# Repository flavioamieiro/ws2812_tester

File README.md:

A simple tester for ws2812 LED strips.

Just plug into USB for power, connect to an LED strip and check if everything
is working.

The software in this repository is licensed under the GPLv2 and the hardware
under the CERN-OHL-S v2.

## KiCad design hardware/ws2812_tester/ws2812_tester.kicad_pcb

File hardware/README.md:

Kicad project with schematics and PCB layout for the ws2812 tester project.

This source describes Open Hardware and is licensed under the CERN-OHL-S v2.
You may redistribute and modify this source and make products using it under
the terms of the CERN-OHL-S v2 (https://ohwr.org/cern_ohl_s_v2.txt).

This source is distributed WITHOUT ANY EXPRESS OR IMPLIED WARRANTY, INCLUDING
OF MERCHANTABILITY, SATISFACTORY QUALITY AND FITNESS FOR A PARTICULAR PURPOSE.
Please see the CERN-OHL-S v2 for applicable conditions.

Source location: https://github.com/flavioamieiro/ws2812_tester

As per CERN-OHL-S v2 section 4, should You produce hardware based on this
source, You must where practicable maintain the Source Location visible on the
external case of the Gizmo or other products you make using this source.

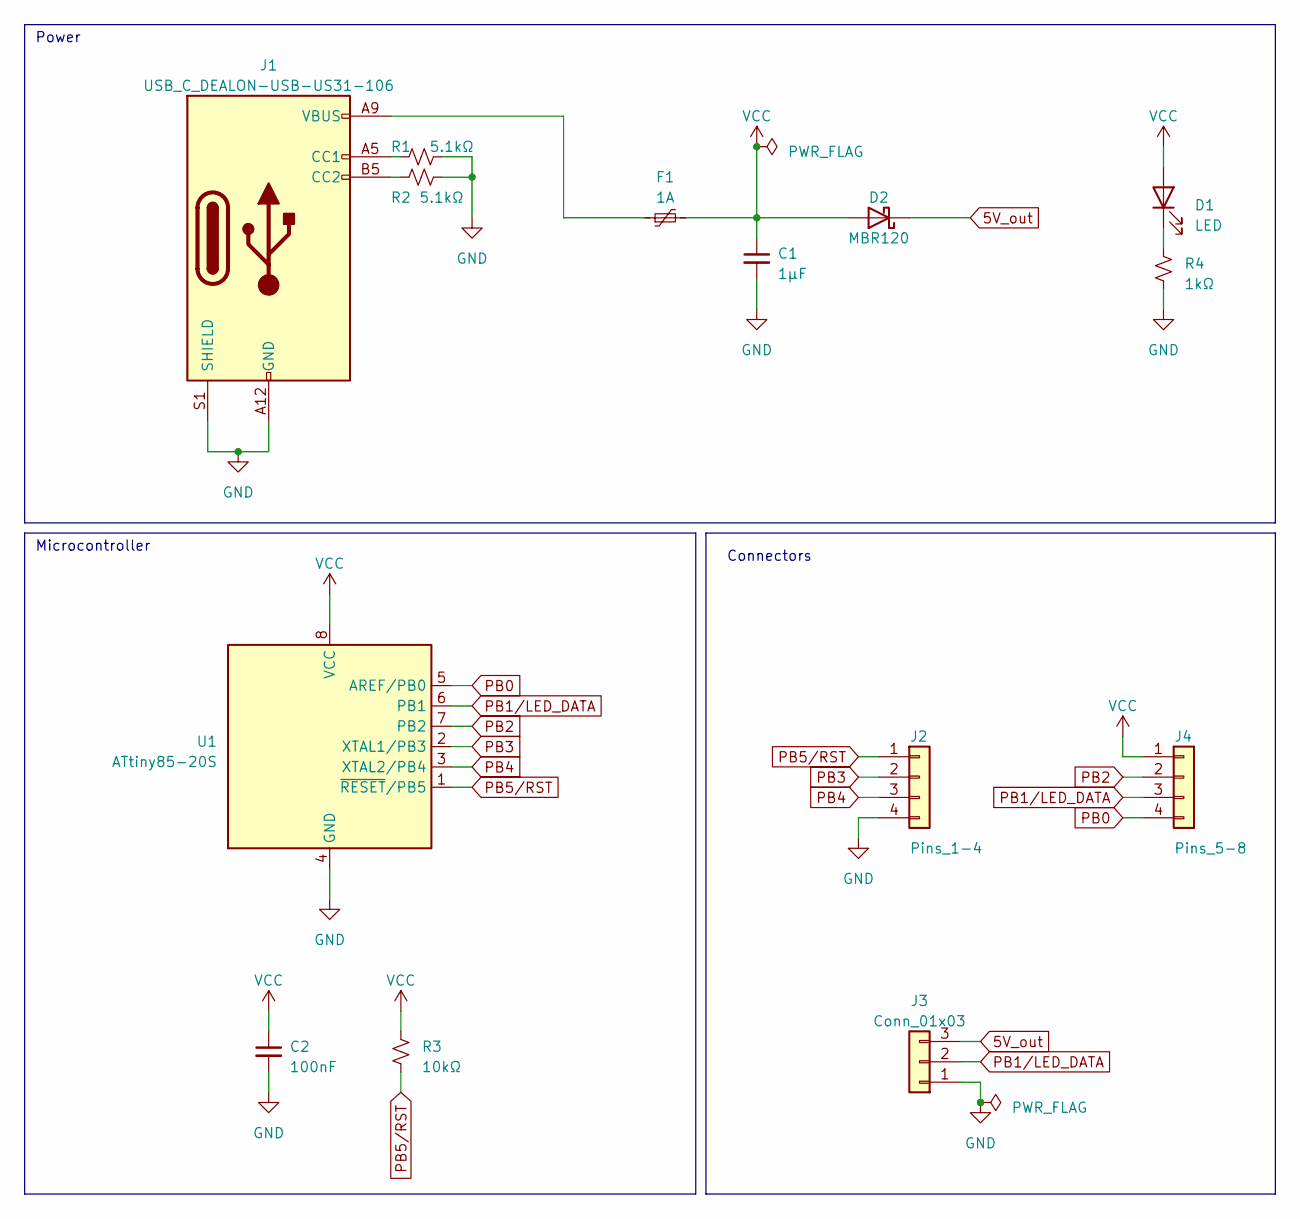
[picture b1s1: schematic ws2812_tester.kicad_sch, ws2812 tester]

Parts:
C1: 1µF; C_0805_2012Metric_Pad1.18x1.45mm_HandSolder
C2: 100nF; C_0805_2012Metric_Pad1.18x1.45mm_HandSolder
D1: LED; LED_0603_1608Metric_Pad1.05x0.95mm_HandSolder
D2: MBR120; D_SOD-123
F1: 1A; Belfuse_0ZCJ
J1: USB_C_DEALON-USB-US31-106; DEALON_USB-US31-106
J2: Pins_1-4; PinHeader_1x04_P2.54mm_Vertical
J3: Conn_01x03; PinHeader_1x03_P2.54mm_Horizontal
J4: Pins_5-8; PinHeader_1x04_P2.54mm_Vertical
R1, R2: 5.1kΩ; R_0805_2012Metric_Pad1.20x1.40mm_HandSolder
R3: 10kΩ; R_0805_2012Metric_Pad1.20x1.40mm_HandSolder
R4: 1kΩ; R_0805_2012Metric_Pad1.20x1.40mm_HandSolder
U1: ATtiny85-20S; SOIC-8W_5.3x5.3mm_P1.27mm

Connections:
5V_out: D2.1 (K), J3.3
GND: C1.2, C2.2, J1.A12 (GND), J1.B12 (GND), J1.S1 (SHIELD), J2.4, J3.1, R1.2, R2.2, R4.2, U1.4 (GND)
unnamed: D1.1 (K), R4.1
unnamed: J1.A5 (CC1), R1.1
unnamed: J1.B5 (CC2), R2.1
unnamed: F1.1, J1.A9 (VBUS), J1.B9 (VBUS)
PB0: J4.4, U1.5 (AREF/PB0)
PB1/LED_DATA: J3.2, J4.3, U1.6 (PB1)
PB2: J4.2, U1.7 (PB2)
PB3: J2.2, U1.2 (XTAL1/PB3)
PB4: J2.3, U1.3 (XTAL2/PB4)
PB5/RST: J2.1, R3.2, U1.1 (~RESET/PB5)
VCC: C1.1, C2.1, D1.2 (A), D2.2 (A), F1.2, J4.1, R3.1, U1.8 (VCC)

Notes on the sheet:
Connectors
Microcontroller
Power

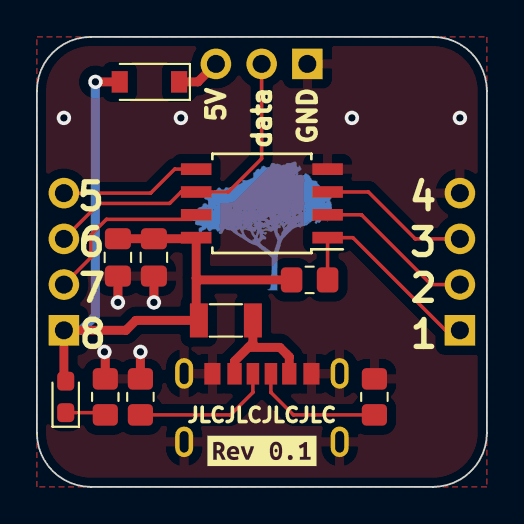
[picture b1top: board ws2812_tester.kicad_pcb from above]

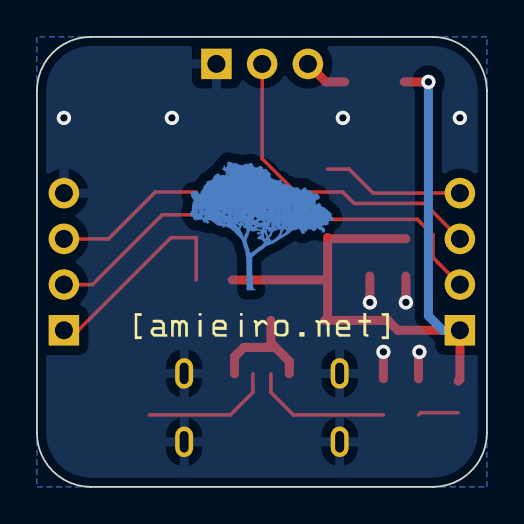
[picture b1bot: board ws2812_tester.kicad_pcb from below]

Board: 2 copper layers, 25.0 x 25.0 mm, 17 parts (3 on the bottom side), 13 nets.

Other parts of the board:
Ref**: Val**; url_bsilks
Ref**#2: Val**; ipe_logo
kibuzzard-625BD852: G***; kibuzzard-625BD852

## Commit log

2022-04-15 Adds empty kicad project for the hardware
2022-04-15 Adds DEALON_USB-US31-106 symbol and footprint
    We'll use this usb-c connector for power only.
2022-04-15 Adds first version of the schematics
2022-04-15 Associates footprints with symbols
2022-04-15 First draft component positioning
2022-04-16 Adds power indication LEDs
2022-04-16 Adjusts component alignment
2022-04-16 Draft routing for all tracks
2022-04-16 Fixes some DRC errors
2022-04-16 Routes 5v from LED strip on the bottom layer
2022-04-16 Changes schematic so the board is never powered by the LED strip
    The idea is that since this is a tester, it will provide the power to
    the LED strip. We add a schottky diode to protect the board just in case
    it is connected to an already powered strip.
    Since we'll always power the board from a usb-c connector, we don't need
    reverse polarity protection anymore.
2022-04-16 Updates PCB with new schematics
2022-04-16 Hides silkscreen components that are not needed
2022-04-16 Moves LED connector closer to the edge
2022-04-16 Adds labels for the Pins
2022-04-16 Adds logo
2022-04-16 Adds a couple of stitching vias on the top of the PCB
2022-04-17 Adds JLCPCB order number placeholder
2022-04-17 Adds revision number to PCB
2022-04-17 Sets Gerber output directory
2022-05-29 Adds simple firmware for testing LED strips based on FAB_LED
    This is basically copied from the examples in FAB_LED[1]. FAB_LED is a
    very compact library for controlling ws2812 (and other) LEDs and lets
    you control a very large number of pixels with very little memory usage.
    To work on an attiny85 you need to set the microcontroller to use
    internal PLL for a 16MHz clock.
    [1]: https://github.com/sonyhome/FAB_LED
2022-05-29 Adds hardware licensing information
2022-05-29 Adds license information for software
    This is GPLv2 since it's based on FAB_LED which is released under this
    license.
